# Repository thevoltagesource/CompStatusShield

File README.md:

# Compressor Status PCB
## Wemos D1 Mini Shield to monitor the A/C control signals.

My A/C has a two stage compressor.  The system should run on stage 1 the majority of the time and run on stage 2 when the
themostat detects a temperture delta at or greater than the programmed value.  Unfortunatly the thermostat doesn't report
what stage is engaged, only that the system is cooling. More importantly, the thermostat will cool beyond the temperature 
set point to lower the humidity in the house but it does not report this state to the cloud service.  Since I want to 
track when the A/C is running I had to find a creative way of monitoring the system. And this little project came to be.

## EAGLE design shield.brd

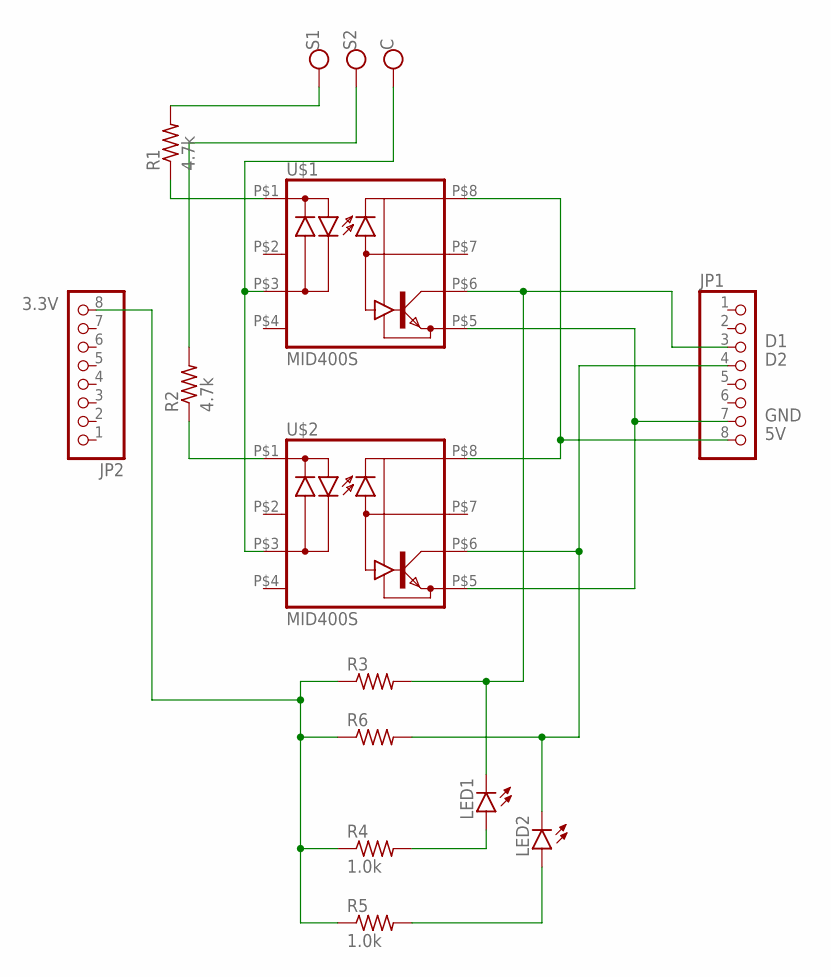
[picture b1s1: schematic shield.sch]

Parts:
JP1, JP2: PINHD-1X8/OCT; 1X08/OCT
LED1, LED2: LEDSML0603; SML0603
R1, R2: 4.7k; R0603
R3, R6: R-US_R0603; R0603
R4, R5: 1.0k; R0603
U$1, U$2: MID400S; SMT8
X1: AK550/3QUIET; AK550/3-N

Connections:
3.3V: JP2.8, R3.1, R4.1, R5.1, R6.1
5V: JP1.8, U$1.P$8 (VCC), U$2.P$8 (VCC)
C: U$1.P$3 (AC2), U$2.P$3 (AC2), X1.1
D1: JP1.3, LED1.C, R3.2, U$1.P$6 (VO)
D2: JP1.4, LED2.C, R6.2, U$2.P$6 (VO)
GND: JP1.7, U$1.P$5 (GND), U$2.P$5 (GND)
unnamed: R2.1, U$2.P$1 (AC1)
unnamed: R1.1, U$1.P$1 (AC1)
unnamed: LED2.A, R5.2
unnamed: LED1.A, R4.2
S1: R1.2, X1.3
S2: R2.2, X1.2

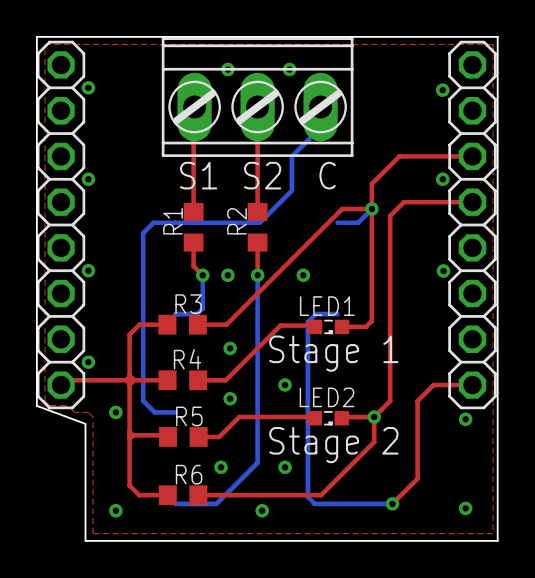
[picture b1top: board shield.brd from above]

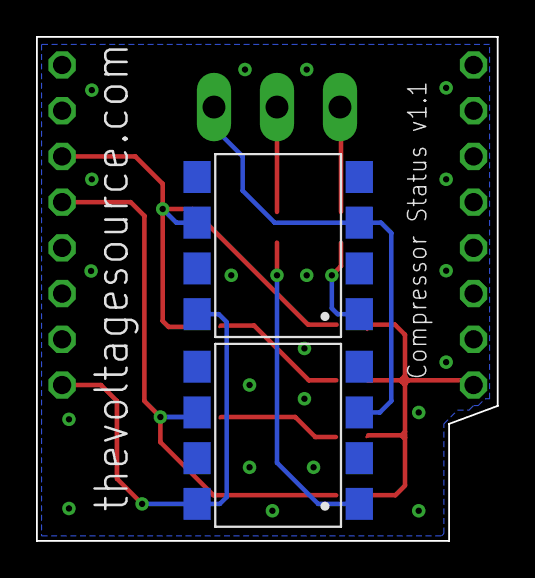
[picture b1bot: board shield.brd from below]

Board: 2 copper layers, 25.6 x 28.0 mm, 13 parts (2 on the bottom side), 12 nets.

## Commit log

2019-08-08 Version 1.0 as ordered from OSHPark
2019-08-08 What is this thing?
2019-11-20 Parts list
2019-11-21 board tweaks, bom fix, local library added
